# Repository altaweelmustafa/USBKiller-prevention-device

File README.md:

# USBKiller-prevention-device
#### This is a repository for COMP332 project

You can find a **detailed explaination** here: [LINK](https://altaweelmustafa.github.io/USB-Killer-Slides/)

---

Contributors:
- [Mustafa Altaweel](https://github.com/altaweelmustafa)
- [Samaa Kali](https://github.com/kaliSamaa)

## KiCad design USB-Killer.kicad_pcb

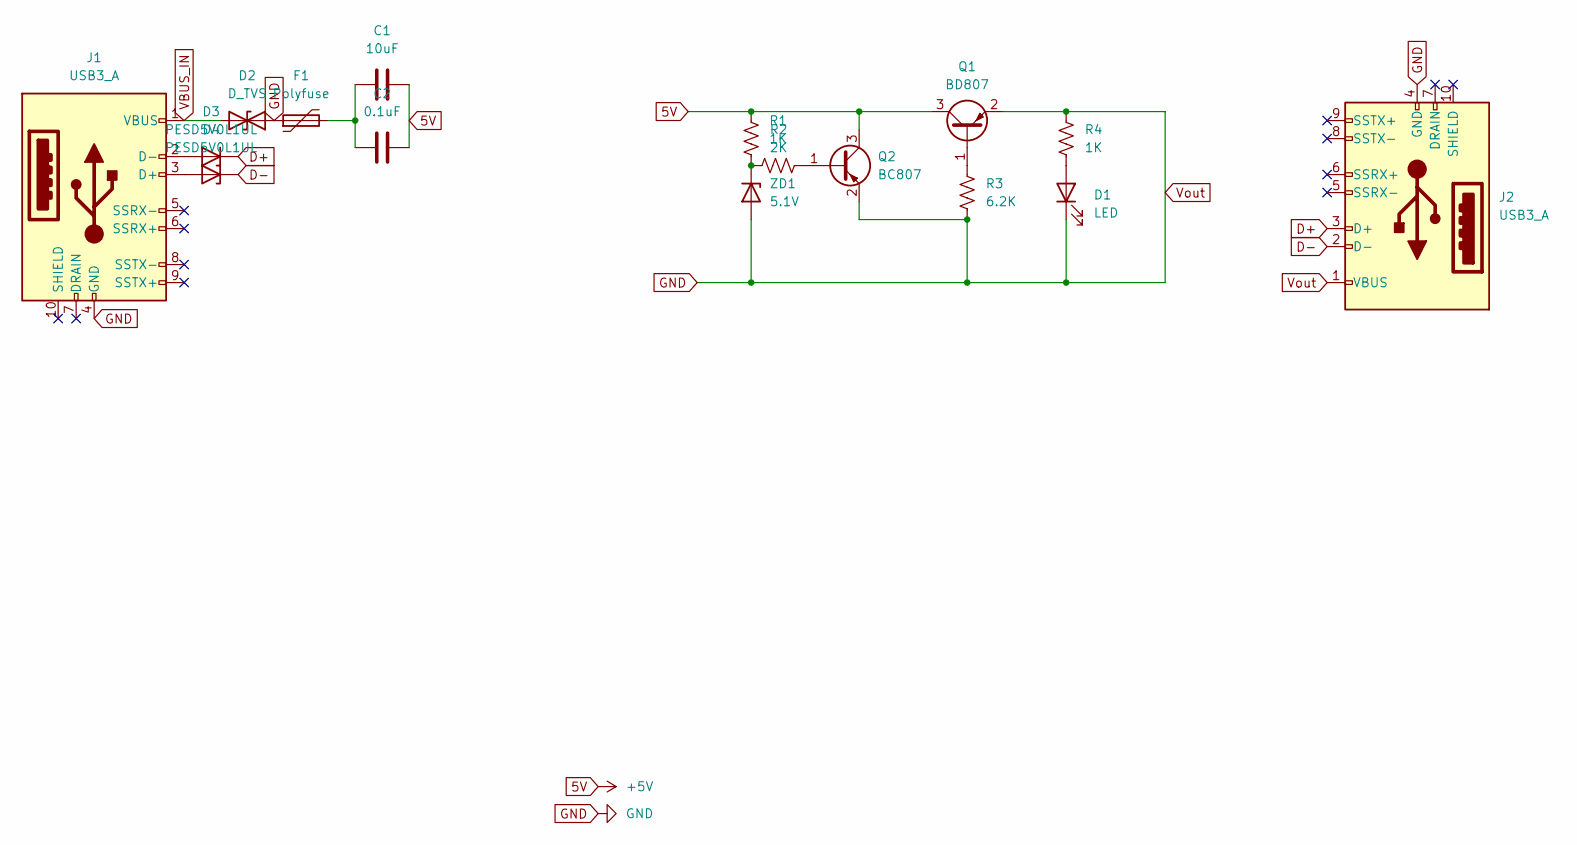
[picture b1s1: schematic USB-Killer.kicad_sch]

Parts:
C1: 10uF; CP_Elec_3x5.3
C2: 0.1uF; CP_Elec_3x5.3
D1: LED; LED_0402_1005Metric
D2: D_TVS; D_0805_2012Metric
D3, D4: PESD5V0L1UL; D_SOD-882
F1: Polyfuse; Fuse_Bourns_MF-RG300
J1: USB3_A; USB3_A_Receptacle_Wuerth_692122030100
J2: USB3_A; USB3_A_Molex_48393-001
Q1: BD807; SOT-23
Q2: BC807; SOT-23
R1, R4: 1K; R_0805_2012Metric
R2: 2K; R_0805_2012Metric
R3: 6.2K; R_0805_2012Metric
ZD1: 5.1V; D_0201_0603Metric

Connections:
5V: C1.2, C2.2, Q1.3 (C), Q2.3 (C), R2.2
D+: D3.1 (K), J2.3 (D+)
D-: D4.1 (K), J2.2 (D-)
GND: D1.1 (K), D2.1 (A1), F1.1, J1.4 (GND), J2.1 (VBUS), J2.4 (GND), Q1.2 (E), Q2.2 (E), R3.2, R4.1, ZD1.2 (A)
unnamed: C1.1, C2.1, F1.2
unnamed: D1.2 (A), R4.2
unnamed: D3.2 (A), J1.2 (D-)
unnamed: D4.2 (A), J1.3 (D+)
unnamed: Q1.1 (B), R3.1
unnamed: Q2.1 (B), R1.2
unnamed: R1.1, R2.1, ZD1.1 (K)
VBUS_IN: D2.2 (A2), J1.1 (VBUS)

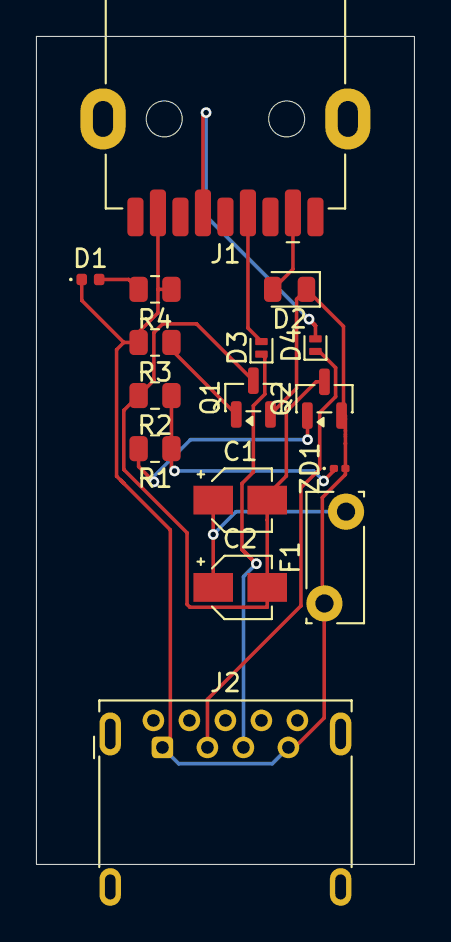
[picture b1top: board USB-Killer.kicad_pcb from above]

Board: 2 copper layers, 21.0 x 46.0 mm, 16 parts (0 on the bottom side), 12 nets.

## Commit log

2025-11-15 proposal
2025-11-15 init schem
2025-11-15 init schem/pcb
2025-11-15 trash
2026-03-18 add slides link
2026-03-18 add contributors
